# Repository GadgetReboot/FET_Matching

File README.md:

# FET_Matching
N Channel JFET Matching PCB<br>
Used with a multimeter to read VGS on a JFET so that it acts like a 10K resistor.<br>
eg.  Some JFETs may look like a 10K resistor when VGS = -1.5v<br>
while others look like a 10K resistor when VGS = -0.350v<br>
FETs can be measured and sorted in groups with similar VGS specs when needed.
<br><br><BR><BR>

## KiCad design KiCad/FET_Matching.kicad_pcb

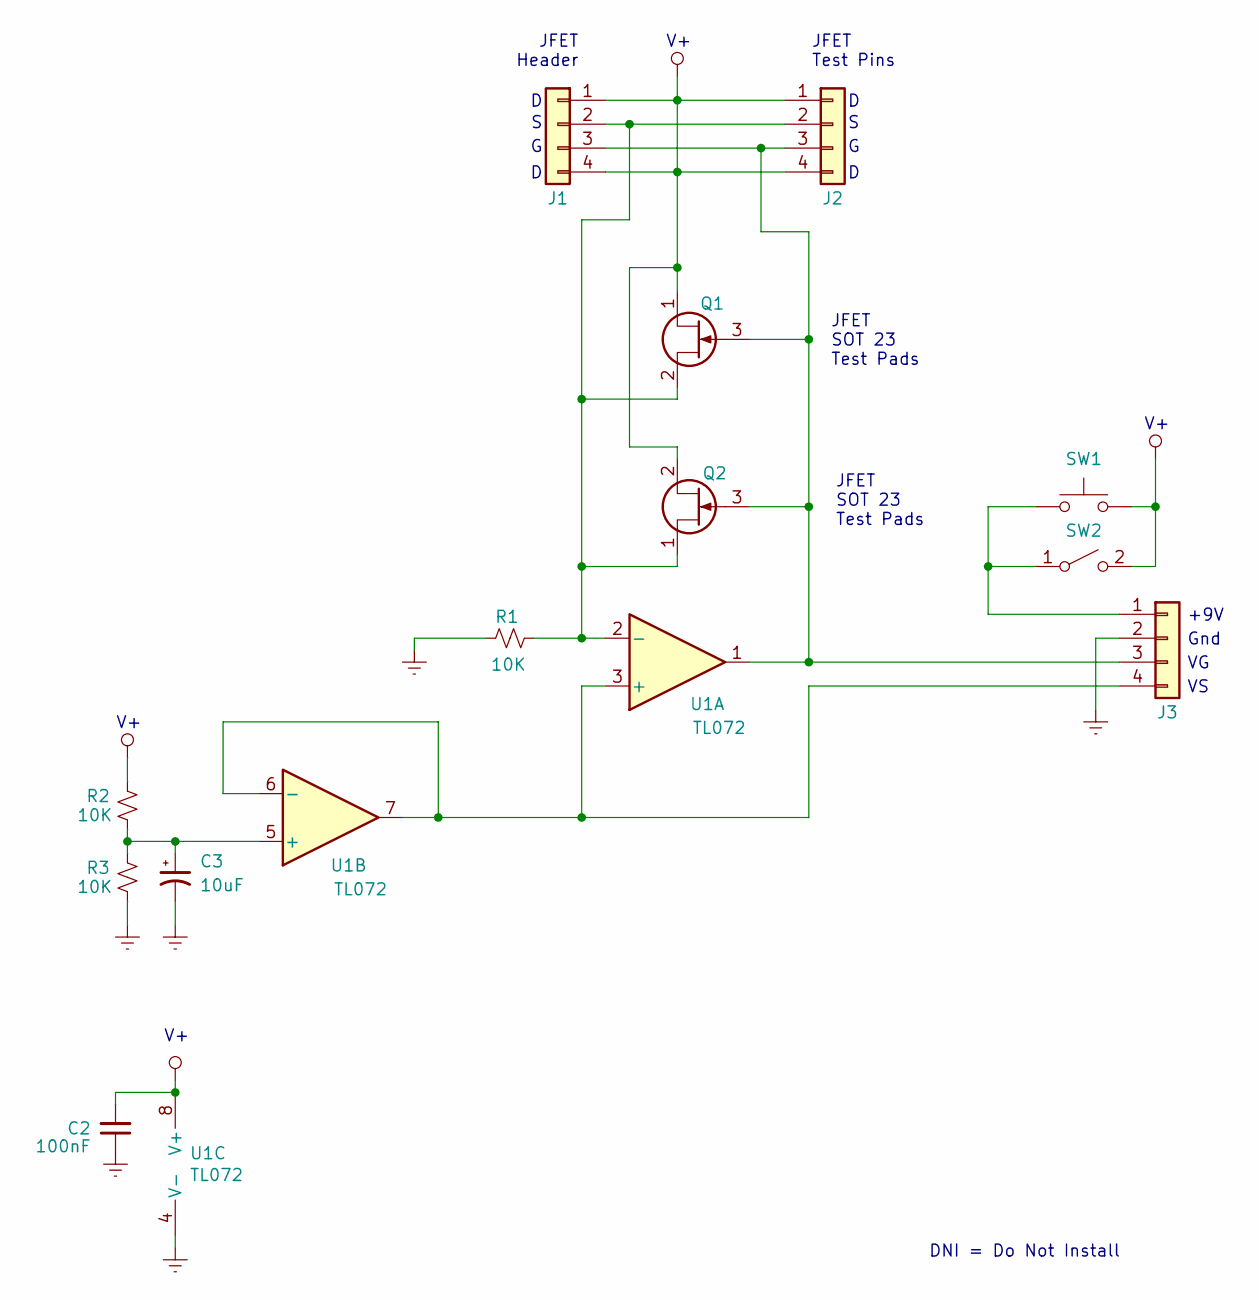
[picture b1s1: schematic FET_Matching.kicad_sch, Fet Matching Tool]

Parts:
C2: 100nF; C_Disc_D3.4mm_W2.1mm_P2.50mm
C3: 10uF; CP_Radial_D5.0mm_P2.50mm
J1, J2, J3: Conn_01x04; PinHeader_1x04_P2.54mm_Vertical
Q1: BSR56; SOT-23
Q2: BF545C; SOT-23
R1, R2, R3: 10K; R_Axial_DIN0309_L9.0mm_D3.2mm_P12.70mm_Horizontal
SW1: SW_Push; PushButton
SW2: SW_SPST; SW_Slide-03_Wuerth-WS-SLTV_10x2.5x6.4_P2.54mm
U1: TL072; DIP-8_W7.62mm

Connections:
GNDREF: C2.1, C3.2, J3.2, R1.2, R3.2, U1.4 (V-)
unnamed: J1.2, J2.2, Q1.2 (S), Q2.1 (S), R1.1, U1.2 (-)
unnamed: J1.3, J2.3, J3.3, Q1.3 (G), Q2.3 (G), U1.1
unnamed: J3.1, SW1.1, SW2.1 (A)
unnamed: J3.4, U1.3 (+), U1.6 (-), U1.7
unnamed: C3.1, R2.2, R3.1, U1.5 (+)
VCC: C2.2, J1.1, J1.4, J2.1, J2.4, Q1.1 (D), Q2.2 (D), R2.1, SW1.2, SW2.2 (B), U1.8 (V+)

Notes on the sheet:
+9V
JFET SOT 23 Test Pads
Gnd
JFET Test Pins
JFET Header
DNI = Do Not Install

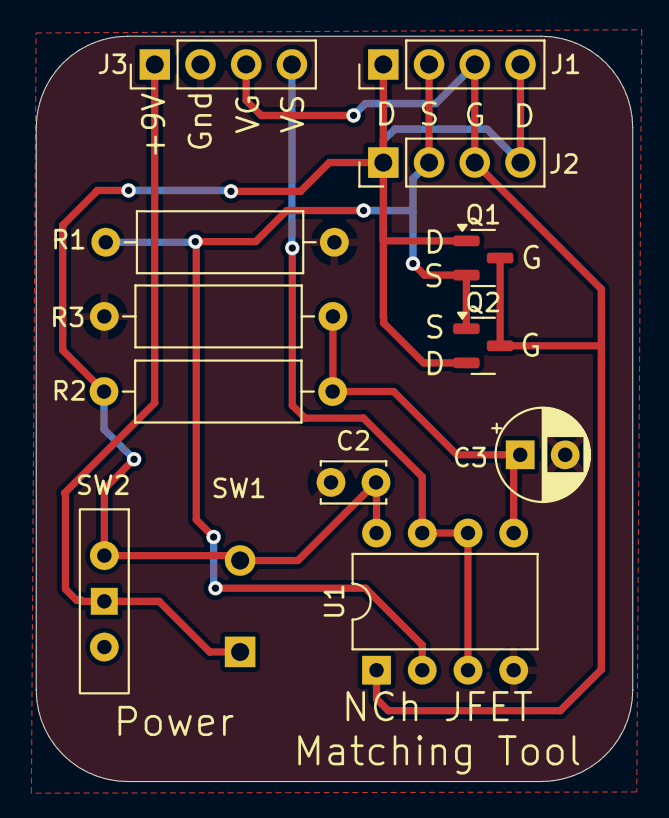
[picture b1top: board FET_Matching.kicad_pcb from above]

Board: 2 copper layers, 33.1 x 41.4 mm, 13 parts (0 on the bottom side), 7 nets.
